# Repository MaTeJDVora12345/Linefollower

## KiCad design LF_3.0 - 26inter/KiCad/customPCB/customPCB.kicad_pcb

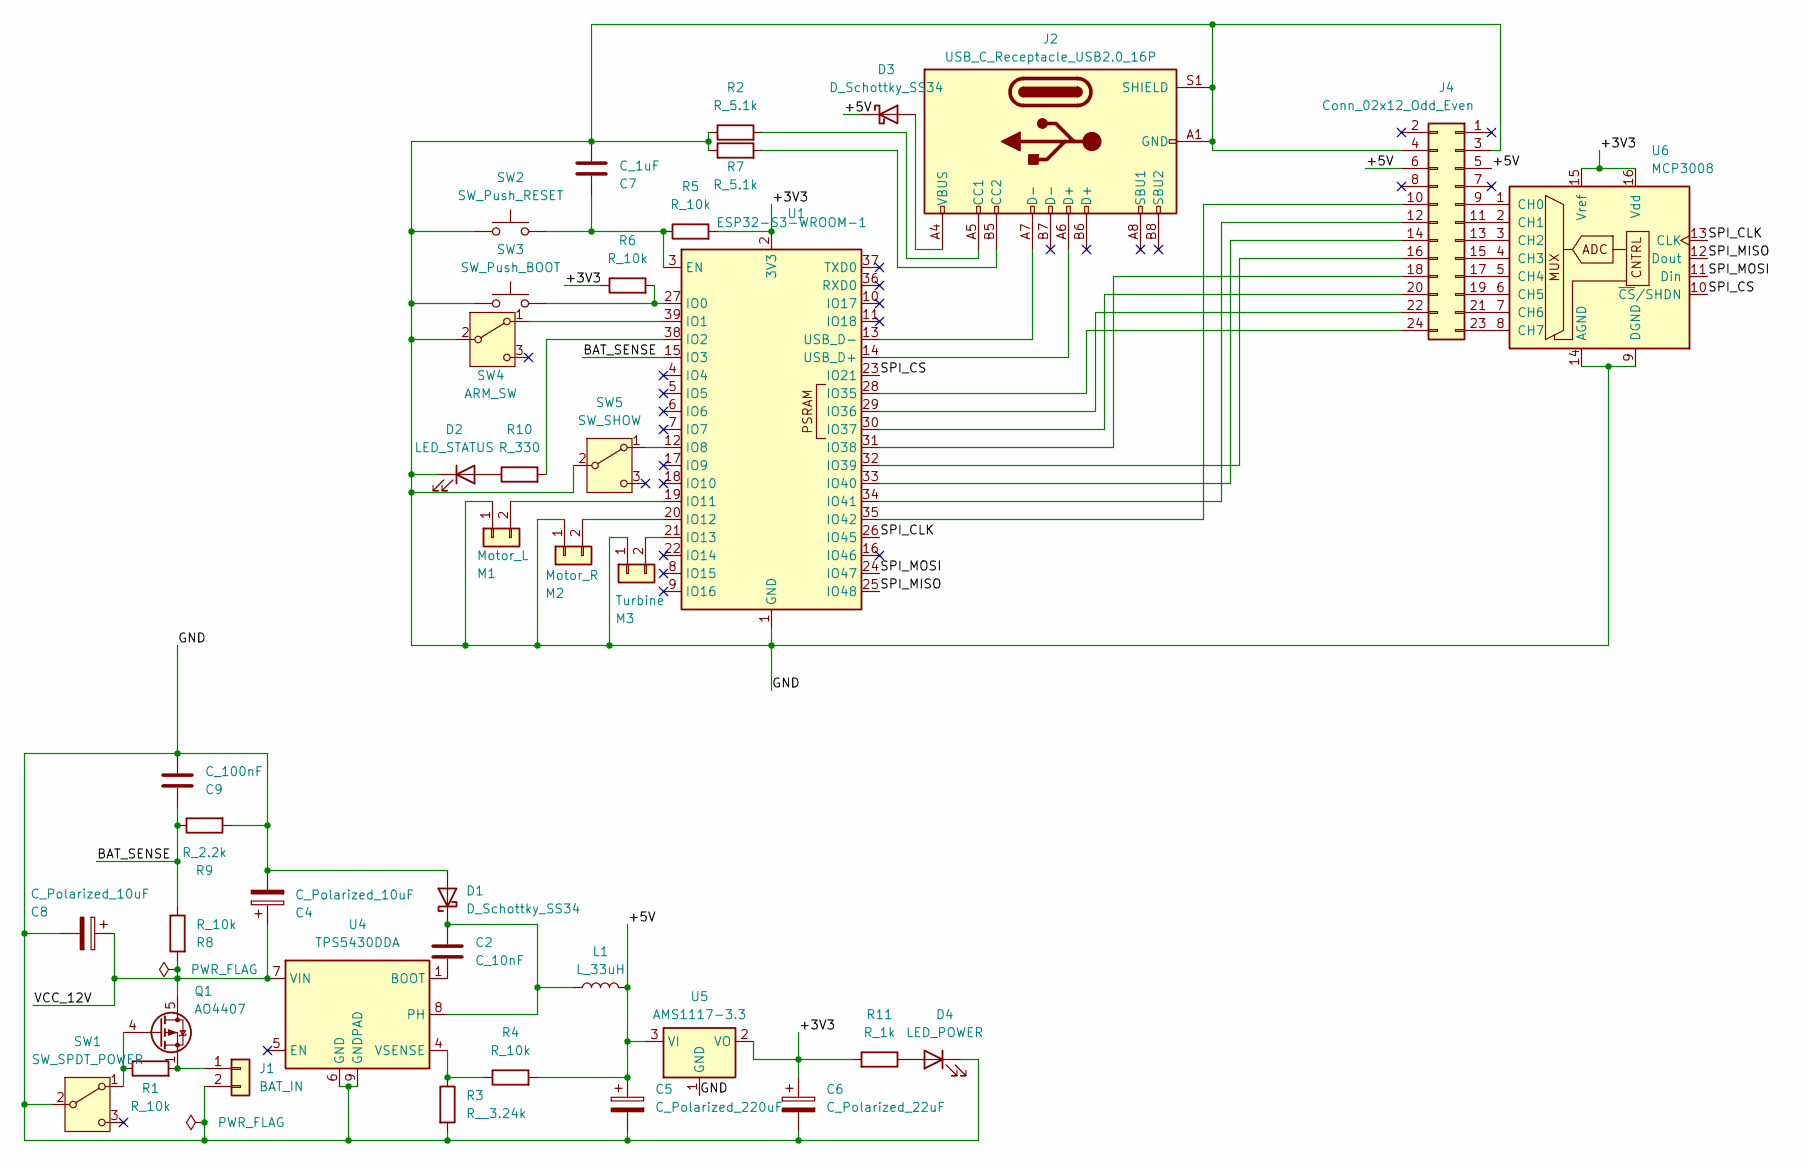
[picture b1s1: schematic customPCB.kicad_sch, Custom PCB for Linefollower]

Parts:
C2: C_10nF; C_0603_1608Metric
C4, C8: C_Polarized_10uF; C_1206_3216Metric
C5: C_Polarized_220uF; CP_Elec_6.3x5.4
C6: C_Polarized_22uF; C_1206_3216Metric
C7: C_1uF; C_0603_1608Metric
C9: C_100nF; C_0603_1608Metric
D1, D3: D_Schottky_SS34; D_SMA
D2: LED_STATUS; LED_0603_1608Metric
D4: LED_POWER; LED_0603_1608Metric
J1: BAT_IN; AMASS_XT60-F_1x02_P7.20mm_Vertical
J2: USB_C_Receptacle_USB2.0_16P; USB_C_Receptacle_GCT_USB4085
J4: Conn_02x12_Odd_Even; IDC-Header_2x12_P2.54mm_Vertical_3D
L1: L_33uH; L_Taiyo-Yuden_NR-60xx
M1: Motor_L; JST_XH_B2B-XH-A_1x02_P2.50mm_Vertical
M2: Motor_R; JST_XH_B2B-XH-A_1x02_P2.50mm_Vertical
M3: Turbine; JST_XH_B2B-XH-A_1x02_P2.50mm_Vertical
Q1: AO4407; SOIC-8_3.9x4.9mm_P1.27mm
R1, R4, R5, R6, R8: R_10k; R_0603_1608Metric
R2, R7: R_5.1k; R_0603_1608Metric
R3: R__3.24k; R_0603_1608Metric
R9: R_2.2k; R_0603_1608Metric
R10: R_330; R_0603_1608Metric
R11: R_1k; R_0603_1608Metric
SW1: SW_SPDT_POWER; SW_SPDT_PCM12
SW2: SW_Push_RESET; SW_SPST_B3U-1000P
SW3: SW_Push_BOOT; SW_SPST_B3U-1000P
SW4: ARM_SW; SW_SPDT_PCM12
SW5: SW_SHOW; SW_SPDT_PCM12
U1: ESP32-S3-WROOM-1
U4: TPS5430DDA; TI_SO-PowerPAD-8_ThermalVias
U5: AMS1117-3.3; SOT-223-3_TabPin2
U6: MCP3008; SOIC-16_3.9x9.9mm_P1.27mm

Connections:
/+3V3: C6.1, R5.2, R6.1, R11.2, U1.2 (3V3), U5.2 (VO), U6.15 (Vref), U6.16 (Vdd)
/+5V: C5.1, D3.1 (K), J4.5, J4.6, L1.2, R4.2, U5.3 (VI)
/BAT_SENSE: C9.1, R8.1, R9.1, U1.15 (IO3)
/GND: C4.2, C5.2, C6.2, C7.2, C8.2, C9.2, D1.2 (A), D2.1 (K), D4.1 (K), J1.2, J2.A1 (GND), J2.A12 (GND), J2.B1 (GND), J2.B12 (GND), J2.S1 (SHIELD), J4.3, J4.4, M1.1, M2.1, M3.1, R2.1, R3.2, R7.1, R9.2, SW1.2 (B), SW2.1, SW3.1, SW4.2 (B), SW5.2 (B), U1.1 (GND), U1.40 (GND), U1.41 (GND), U4.6 (GND), U4.9 (GNDPAD), U5.1 (GND), U6.9 (DGND), U6.14 (AGND)
/SPI_CLK: U1.26 (IO45), U6.13 (CLK)
/SPI_CS: U1.23 (IO21), U6.10 (~CS/SHDN)
/SPI_MISO: U1.25 (IO48), U6.12 (Dout)
/SPI_MOSI: U1.24 (IO47), U6.11 (Din)
/VCC_12V: C4.1, C8.1, Q1.5 (D), Q1.6 (D), Q1.7 (D), Q1.8 (D), R8.2, U4.7 (VIN)
unnamed: C2.1, D1.1 (K), L1.1, U4.8 (PH)
unnamed: D2.2 (A), R10.1
unnamed: D3.2 (A), J2.A4 (VBUS), J2.A9 (VBUS), J2.B4 (VBUS), J2.B9 (VBUS)
unnamed: D4.2 (A), R11.1
unnamed: J1.1, Q1.1 (S), Q1.2 (S), Q1.3 (S), R1.2
unnamed: J2.A5 (CC1), R2.2
unnamed: J2.B5 (CC2), R7.2
unnamed: J4.9, U6.1 (CH0)
unnamed: J4.10, U1.35 (IO42)
unnamed: J4.11, U6.2 (CH1)
unnamed: J4.12, U1.34 (IO41)
unnamed: J4.13, U6.3 (CH2)
unnamed: J4.14, U1.33 (IO40)
unnamed: J4.15, U6.4 (CH3)
unnamed: J4.16, U1.32 (IO39)
unnamed: J4.17, U6.5 (CH4)
unnamed: J4.18, U1.31 (IO38)
unnamed: J4.19, U6.6 (CH5)
unnamed: J4.20, U1.30 (IO37)
unnamed: J4.21, U6.7 (CH6)
unnamed: J4.22, U1.29 (IO36)
unnamed: J4.23, U6.8 (CH7)
unnamed: J4.24, U1.28 (IO35)
unnamed: M1.2, U1.19 (IO11)
unnamed: M2.2, U1.20 (IO12)
unnamed: M3.2, U1.21 (IO13)
unnamed: Q1.4 (G), R1.1, SW1.1 (A)
unnamed: SW4.1 (A), U1.39 (IO1)
unnamed: SW5.1 (A), U1.12 (IO8)
unnamed: C7.1, R5.1, SW2.2, U1.3 (EN)
unnamed: R6.2, SW3.2, U1.27 (IO0)
unnamed: R10.2, U1.38 (IO2)
unnamed: J2.A6 (D+), U1.14 (USB_D+)
unnamed: J2.A7 (D-), U1.13 (USB_D-)
unnamed: C2.2, U4.1 (BOOT)
unnamed: R3.1, R4.1, U4.4 (VSENSE)

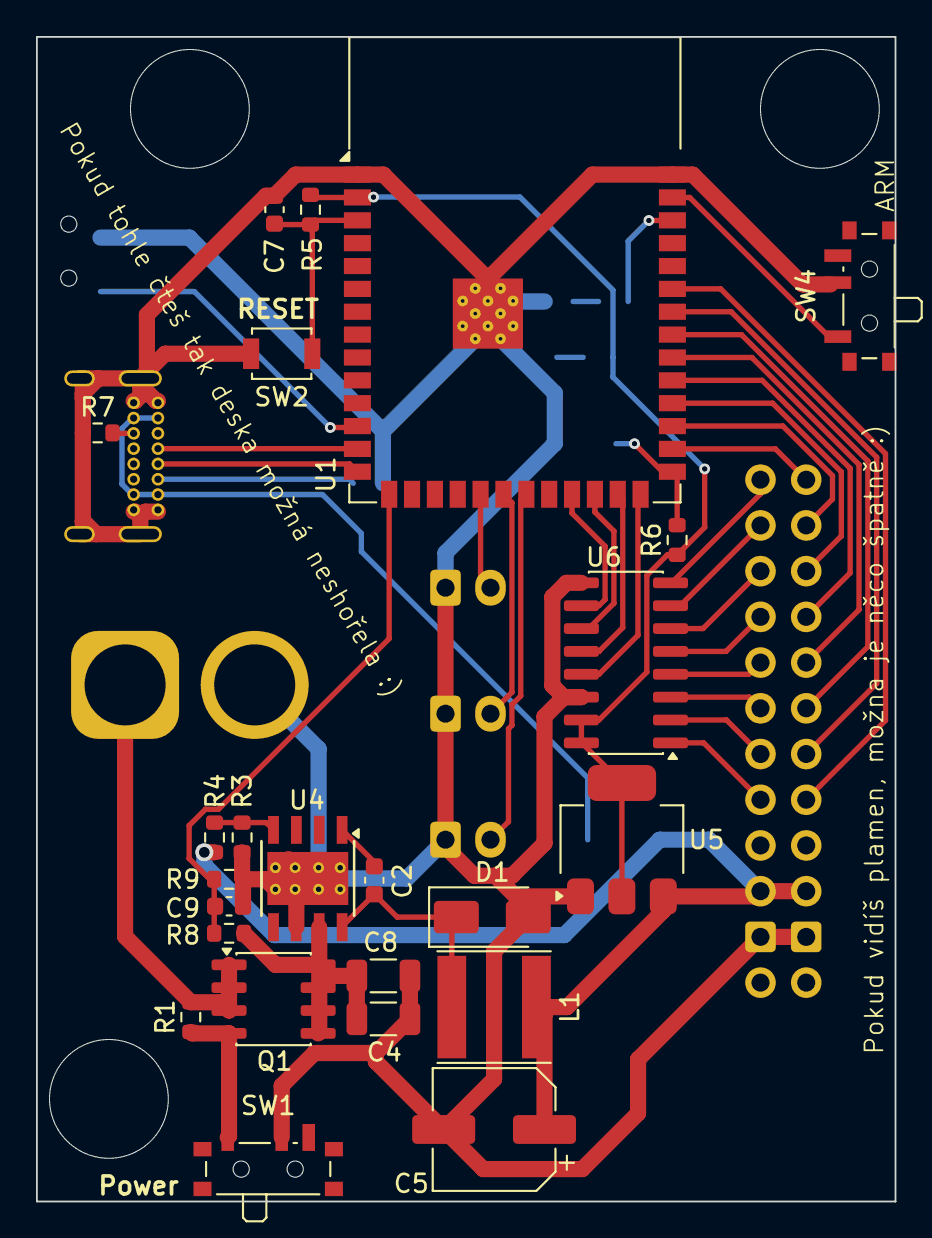
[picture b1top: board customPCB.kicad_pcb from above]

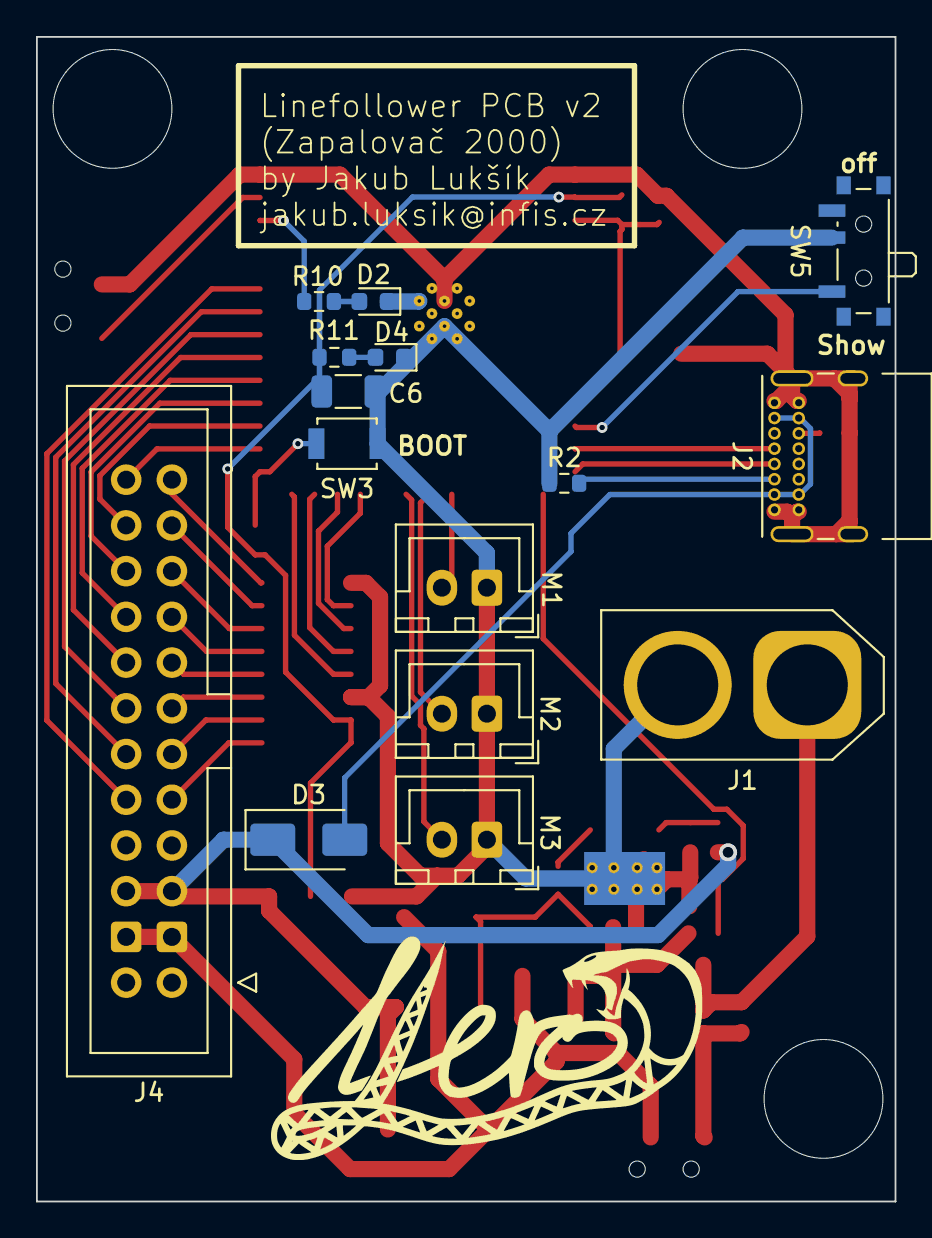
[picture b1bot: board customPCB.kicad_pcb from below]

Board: 2 copper layers, 47.7 x 64.7 mm, 39 parts (15 on the bottom side), 45 nets.

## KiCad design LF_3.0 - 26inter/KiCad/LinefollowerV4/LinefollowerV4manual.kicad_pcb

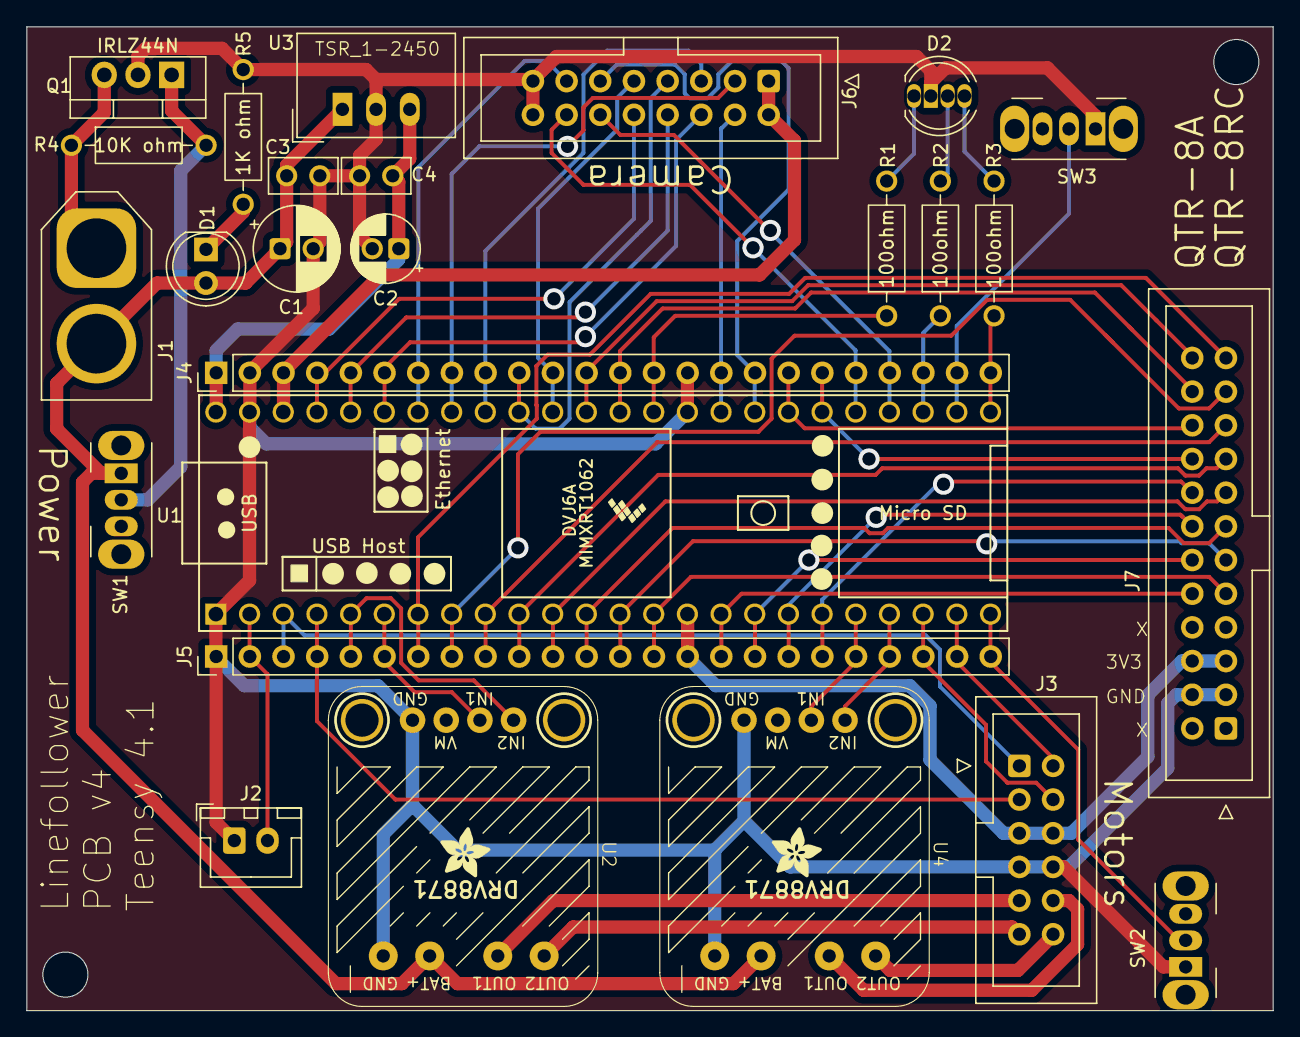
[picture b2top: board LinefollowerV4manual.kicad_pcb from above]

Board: 2 copper layers, 94.0 x 74.2 mm, 26 parts (0 on the bottom side), 57 nets.

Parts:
C1: 100µF / 25V; CP_Radial_D6.3mm_P2.50mm
C2: 10µF / 16V; CP_Radial_D5.0mm_P2.00mm
C3, C4: 100nF; C_Disc_D5.0mm_W2.5mm_P2.50mm
D1: LED; LED_D5.0mm
D2: LED_RKGB; LED_RKBG_D5.0mm-4_RGB
J1: Conn_01x02; AMASS_XT60-M_1x02_P7.20mm_Vertical
J2: JST_XH_B2B-XH-A_1x02_P2.50mm_Vertical
J3: Polulu 25d gearmotor encoder; IDC-Header_2x06_P2.54mm_Vertical
J4, J5: Conn_01x24; PinHeader_1x24_P2.54mm_Vertical
J6: Conn_02x08_ArduCam_Himax_HM01B0; IDC-Header_2x08_P2.54mm_Vertical
J7: Conn_02x12_Odd_Even; IDC-Header_2x12_P2.54mm_Vertical_3D
Q1: IRLZ44N; TO-220-3_Vertical
R1, R3: 100ohm; R_Axial_DIN0207_L6.3mm_D2.5mm_P10.16mm_Horizontal
R2: R; R_Axial_DIN0207_L6.3mm_D2.5mm_P10.16mm_Horizontal
R4: 10k; R_Axial_DIN0207_L6.3mm_D2.5mm_P10.16mm_Horizontal
R5: 1k; R_Axial_DIN0207_L6.3mm_D2.5mm_P10.16mm_Horizontal
SW1, SW2, SW3: SW_SPDT; SW_Slide_SPDT_Angled_CK_OS102011MA1Q
U1: Teensy4.1; Teensy41
U2, U4: DRV8871 Breakout Board
U3: TSR_1-2450; Converter_DCDC_TRACO_TSR-1_THT

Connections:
unnamed: C1.1, C3.1, D1.2 (A), J1.2, SW1.1 (A), U2.7 (VM-BAT+), U3.1 (Vin), U4.7 (VM-BAT+)
unnamed: D1.1 (K), R5.2
unnamed: D2.4 (BA), R3.2
unnamed: D2.3 (GA), R2.2
unnamed: C1.2, C2.2, C3.2, C4.2, D2.2 (K), J2.1, J3.7 (EncGND), J3.8 (EncGND), J4.2, J4.15, J5.1, J6.15 (GND), J6.16 (GND), J7.3, J7.4, Q1.2 (D), R5.1, SW2.1 (A), SW3.1 (A), U1.1 (GND), U1.34 (GND), U1.47 (GND), U2.1 (GND), U2.8 (GND), U3.2 (GND), U4.1 (GND), U4.8 (GND)
unnamed: D2.1 (RA), R1.2
unnamed: J1.1, Q1.3 (S), R4.1
unnamed: J2.2, J5.2, U1.2 (0_RX1_CRX2_CS1)
unnamed: C2.1, C4.1, J4.1, U1.48 (VIN), U3.3 (Vout)
unnamed: J4.3, J6.1 (VCC), J6.2 (VCC), U1.46 (3V3)
unnamed: J4.4, J6.10 (D3), U1.45 (23_A9_CRX1_MCLK1)
unnamed: J4.5, J6.8 (D2), U1.44 (22_A8_CTX1)
unnamed: J4.6, J6.6 (D1), U1.43 (21_A7_RX5_BCLK1)
unnamed: J4.7, J6.13 (D0), U1.42 (20_A6_TX5_LRCLK1)
unnamed: J4.8, J6.3 (SCL), U1.41 (19_A5_SCL)
unnamed: J4.9, J6.5 (SDA), U1.40 (18_A4_SDA)
unnamed: J4.10, J6.7 (VSYNC), U1.39 (17_A3_TX4_SDA1)
unnamed: J4.11, J6.9 (HREF), U1.38 (16_A2_RX4_SCL1)
unnamed: J4.12, J7.24, U1.37 (15_A1_RX3_SPDIF_IN)
unnamed: J4.13, J7.22, U1.36 (14_A0_TX3_SPDIF_OUT)
unnamed: J4.14, R1.1, U1.35 (13_SCK_LED)
unnamed: J4.16, J6.4 (XCLK), U1.33 (41_A17)
unnamed: J4.17, J6.11 (PCLK), U1.32 (40_A16)
unnamed: J4.18, J7.20, U1.31 (39_MISO1_OUT1A)
unnamed: J4.19, J7.18, U1.30 (38_CS1_IN1)
unnamed: J4.20, J6.14 (INT), U1.29 (37_CS)
unnamed: J4.21, J6.12 (TRIG), U1.28 (36_CS)
unnamed: J4.22, R2.1, U1.27 (35_TX8)
unnamed: J4.23, SW3.2 (B), U1.26 (34_RX8)
unnamed: J4.24, R3.1, U1.25 (33_MCLK2)
unnamed: J3.1 (EncB), J5.3, U1.3 (1_TX1_CTX2_MISO1)
unnamed: J3.3 (EncA), J5.4, U1.4 (2_OUT2)
unnamed: J5.5, U1.5 (3_LRCLK2), U2.2 (IN2)
unnamed: J5.6, U1.6 (4_BCLK2), U2.3 (IN1)
unnamed: J5.7, J7.23, U1.7 (5_IN2)
unnamed: J5.8, J7.21, U1.8 (6_OUT1D)
unnamed: J5.9, J7.19, U1.9 (7_RX2_OUT1A)
unnamed: J5.10, J7.17, U1.10 (8_TX2_IN1)
unnamed: J5.11, J7.15, U1.11 (9_OUT1C)
unnamed: J5.12, J7.13, U1.12 (10_CS_MQSR)
unnamed: J5.13, J7.11, U1.13 (11_MOSI_CTX1)
unnamed: J5.14, J7.9, U1.14 (12_MISO_MQSL)
unnamed: J3.5 (EncVM), J3.6 (EncVM), J5.15, J7.5, J7.6, U1.15 (3V3)
unnamed: J5.16, J7.10, U1.16 (24_A10_TX6_SCL2)
unnamed: J5.17, J7.12, U1.17 (25_A11_RX6_SDA2)
unnamed: J5.18, J7.14, U1.18 (26_A12_MOSI1)
unnamed: J5.19, J7.16, U1.19 (27_A13_SCK1)
unnamed: J5.20, U1.20 (28_RX7), U4.3 (IN1)
unnamed: J5.21, U1.21 (29_TX7), U4.2 (IN2)
unnamed: J3.4 (EncA), J5.22, U1.22 (30_CRX3)
unnamed: J3.2 (EncB), J5.23, U1.23 (31_CTX3)
unnamed: J5.24, SW2.2 (B), U1.24 (32_OUT1B)
unnamed: Q1.1 (G), R4.2, SW1.2 (B)
unnamed: J3.9 (Mot-), U2.6 (MOTOR1)
unnamed: J3.11 (Mot+), U2.5 (MOTOR2)
unnamed: J3.10 (Mot-), U4.6 (MOTOR1)
unnamed: J3.12 (Mot+), U4.5 (MOTOR2)

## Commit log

2026-03-12 Create todo
2026-03-12 Update main.py
    mby
2026-03-12 jebat
2026-03-12 Update main.py
    ai
2026-03-14 changet repository structure
2026-03-14 added KiCad files to repo
2026-03-14 folder structure
2026-03-16 hello
2026-03-16 added .gitignore and update documentation
2026-03-16 moved senzor test
2026-03-16 first version of technical report
2026-03-17 jebaaaaat
2026-03-18 fuck python. C on top
2026-04-23 renamed
